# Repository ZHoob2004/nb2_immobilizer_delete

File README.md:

# nb2_immobilizer_delete

This board is meant to be installed on the connector pins inside the ECU and disable the immobilizer by providing affirmative responses even when a valid chip is not present.

To use, remove the ecu from the car and open the lid. Align the board with the main connector and solder the 3 circled points, then close and reinstall.

Leaving the factory immobilizer connected, turn the key to the on position and wait for a few seconds. Then turn the key off and disconnect the factory immobilizer module under the steering column.

The car should now start with any working key, regardless of chip pairing.

The rough design and firmware were taken from a miata.net thread, credit to Alcantor

https://forum.miata.net/vb/showthread.php?p=8561544#post8561544

# Build and flash instructions

This firmware targets a **bare ATtiny85 running at 1 MHz** using the calibrated 8 MHz internal RC oscillator with the `CKDIV8` fuse programmed.

## Toolchain

Install these tools:

- `avr-gcc`
- `avr-libc`
- `binutils-avr` / `avr-objcopy`
- `avrdude`

On Debian/Ubuntu/WSL:

```bash
sudo apt update
sudo apt install gcc-avr avr-libc binutils-avr avrdude
```

## Build

From the repository root:

```bash
avr-gcc \
  -Wall -Wextra -Os -std=gnu11 \
  -ffunction-sections -fdata-sections \
  -Wl,--gc-sections \
  -DF_CPU=1000000UL \
  -mmcu=attiny85 \
  -o main.elf main.c

avr-objcopy -j .text -j .data -O ihex main.elf main.hex
avr-objcopy -j .text -j .data -O binary main.elf main.bin
avr-size -C --mcu=attiny85 main.elf
```

`main.hex` is the recommended file for AVRDUDE. `main.bin` is also produced as a raw flash image for releases or other programming tools.

## 1 MHz clock fuse

Use low fuse **`0x62`**:

- internal calibrated 8 MHz RC oscillator
- `CKDIV8` programmed, giving a 1 MHz system clock
- clock output disabled
- default long startup delay retained

Only the low fuse needs to be changed for the 1 MHz clock configuration. Do **not** program `RSTDISBL`; the RESET pin is required for ISP.

You can read the existing fuses before changing anything:

```bash
avrdude -c arduino_as_isp -P COM5 -b 19200 -p t85 \
  -U lfuse:r:-:h -U hfuse:r:-:h -U efuse:r:-:h
```

Replace `COM5` with the programmer's serial port. On Linux/WSL this may be `/dev/ttyACM0` or `/dev/ttyUSB0`.

## Arduino as ISP

Load the standard **ArduinoISP** sketch onto the Arduino programmer first. The current ArduinoISP sketch uses a target SPI clock of approximately 166.7 kHz by default, specifically chosen to be safe for a 1 MHz ATtiny target.

### AVRDUDE 8.x / current programmer name

Set the 1 MHz fuse:

```bash
avrdude -c arduino_as_isp -P COM5 -b 19200 -p t85 \
  -U lfuse:w:0x62:m
```

Flash and verify the HEX file:

```bash
avrdude -c arduino_as_isp -P COM5 -b 19200 -p t85 \
  -U flash:w:main.hex:i \
  -U flash:v:main.hex:i
```

Or write the fuse and firmware in one command:

```bash
avrdude -c arduino_as_isp -P COM5 -b 19200 -p t85 \
  -U lfuse:w:0x62:m \
  -U flash:w:main.hex:i \
  -U flash:v:main.hex:i
```

### Older AVRDUDE installations

If your AVRDUDE does not recognize `arduino_as_isp`, use the STK500v1 programmer definition used by the ArduinoISP sketch:

```bash
avrdude -c stk500v1 -P COM5 -b 19200 -p t85 \
  -U lfuse:w:0x62:m \
  -U flash:w:main.hex:i \
  -U flash:v:main.hex:i
```

The `-b 19200` option is the serial link speed between the PC and the Arduino running ArduinoISP; it is **not** the ISP SCK frequency sent to the ATtiny.

## ISP wiring

ATtiny85 ISP signals are:

| ATtiny85 | ISP function |
|---|---|
| PB0 / pin 5 | MOSI |
| PB1 / pin 6 | MISO |
| PB2 / pin 7 | SCK |
| PB5 / pin 1 | RESET |
| pin 8 | VCC |
| pin 4 | GND |

The application signals are deliberately moved away from the ISP pins:

- `TX_INV` = PB3 / pin 2
- `RX_INV` = PB4 / pin 3

`RX_INV` has an external 10 kOhm pull-up, so the firmware does not enable the ATtiny internal pull-up on PB4.

## EEPROM note

The firmware stores the learned five-byte immobilizer response in EEPROM. A normal AVRDUDE flash operation may perform a chip erase, and the factory-default high fuse does **not** preserve EEPROM through chip erase.

If you intend to reflash a unit after it has learned a code, back up EEPROM first:

```bash
avrdude -c arduino_as_isp -P COM5 -b 19200 -p t85 \
  -U eeprom:r:eeprom-backup.hex:i
```

Restore it afterward if necessary:

```bash
avrdude -c arduino_as_isp -P COM5 -b 19200 -p t85 \
  -U eeprom:w:eeprom-backup.hex:i
```

Alternatively, the `EESAVE` high-fuse bit can be programmed so EEPROM survives chip erase, but that changes the high fuse and should be done deliberately rather than as part of the basic 1 MHz flashing command.

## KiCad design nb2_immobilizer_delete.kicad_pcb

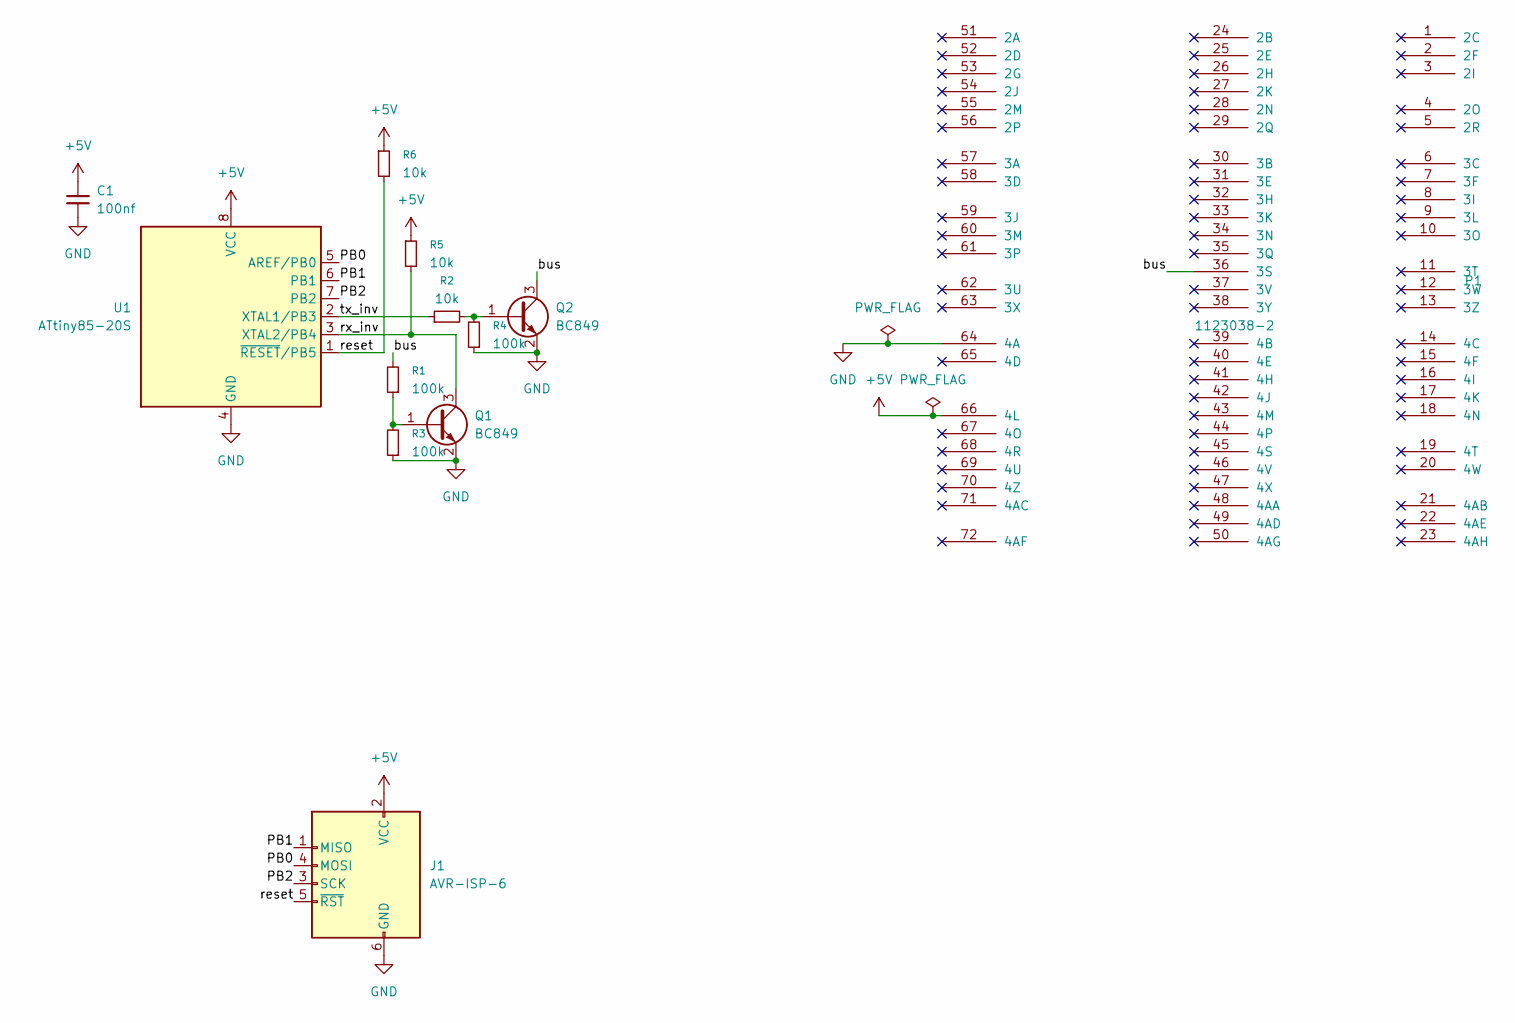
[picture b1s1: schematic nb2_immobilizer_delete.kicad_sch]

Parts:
C1: 100nf; C_0603_1608Metric
J1: AVR-ISP-6; Tag-Connect_TC2030-IDC-NL_2x03_P1.27mm_Vertical
P1: 1123038-2
Q1, Q2: BC849; SOT-23; LCSC Part # C334244
R1, R3, R4: 100k; R_0603_1608Metric; LCSC Part # C25803
R2, R5, R6: 10k; R_0603_1608Metric; LCSC Part # C25804
U1: ATtiny85-20S; SOIC-8_5.3x5.3mm_P1.27mm; LCSC Part # C31540447

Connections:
+5V: C1.1, J1.2 (VCC), P1.66 (4L), R5.1, R6.1, U1.8 (VCC)
/PB0: J1.4 (MOSI), U1.5 (AREF/PB0)
/PB1: J1.1 (MISO), U1.6 (PB1)
/PB2: J1.3 (SCK), U1.7 (PB2)
/bus: P1.36 (3S), Q2.3 (C), R1.2
/reset: J1.5 (~RST), R6.2, U1.1 (~RESET/PB5)
/rx_inv: Q1.3 (C), R5.2, U1.3 (XTAL2/PB4)
/tx_inv: R2.1, U1.2 (XTAL1/PB3)
GND: C1.2, J1.6 (GND), P1.64 (4A), Q1.2 (E), Q2.2 (E), R3.1, R4.1, U1.4 (GND)
unnamed: Q1.1 (B), R1.1, R3.2
unnamed: Q2.1 (B), R2.2, R4.2

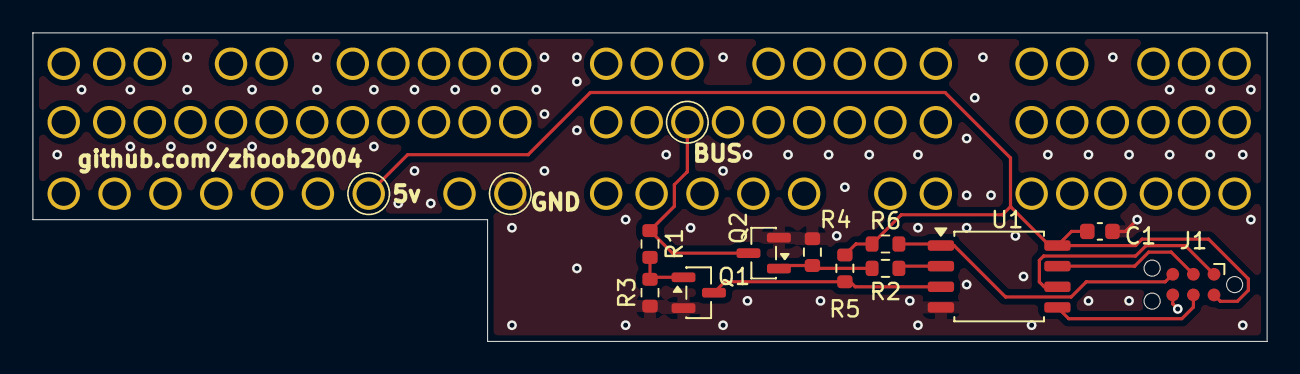
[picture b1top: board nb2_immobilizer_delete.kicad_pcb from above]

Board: 2 copper layers, 76.0 x 19.0 mm, 12 parts (1 on the bottom side), 11 nets.

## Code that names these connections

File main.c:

/**
 * MX5 NBFL Immobilizer Bypass for a bare ATtiny85.
 *
 * Target configuration:
 *   - F_CPU: 1 MHz (8 MHz internal RC oscillator with CKDIV8 enabled)
 *   - TX_INV: PB3
 *   - RX_INV: PB4, with an external 10 kOhm pull-up to VCC
 *   - PB0/PB1/PB2: reserved for ISP only
 */

#ifndef F_CPU
#define F_CPU 1000000UL
#endif

#if F_CPU != 1000000UL
#error "This firmware is configured for a 1 MHz ATtiny85 system clock."
#endif

#include <avr/io.h>
#include <avr/interrupt.h>
#include <avr/eeprom.h>
#include <stdint.h>

#define TX_INV_PIN PB3
#define RX_INV_PIN PB4

#define IMM_CODE_LEN 5

/*
 * Timer1 runs from the 1 MHz system clock divided by 8, giving a 125 kHz
 * timer clock. OCR1A/OCR1B intentionally retain the timing of the original
 * 16 MHz firmware, which used a /128 Timer1 prescaler and therefore the
 * same 125 kHz timer clock.
 */
#define TIMER1_COMPARE_A 80
#define TIMER1_COMPARE_B 105

enum state {
    s_idle,
    s_waitimm,
    s_learn,
    s_simulate
};

static volatile enum state g_state = s_idle;

#define is_reading_byte() (g_readed_bits != 0xFFFF)
#define is_writing_byte() (g_state == s_simulate)

static uint8_t g_imm_code_learn[IMM_CODE_LEN];
static volatile uint8_t g_imm_code[IMM_CODE_LEN];
static volatile uint8_t g_imm_answer_timeout;
static volatile uint8_t g_imm_learn_timeout;
static volatile uint16_t g_readed_bits = 0xFFFF;

static void handle_recv_byte(uint8_t byte);

int main(void)
{
    uint8_t data_in[2] = {1, 1};
    unsigned int i;

    cli();

    /*
     * PB3 is the only application output. Keep TX low so Q2 is off.
     * PB4 remains an input and uses the external 10 kOhm pull-up.
     * PB0/PB1/PB2 are unused during normal operation; enable their internal
     * pull-ups so the exposed ISP pads do not float when no programmer is
     * attached. During reset/ISP, the programming interface takes control.
     */
    DDRB = (1 << TX_INV_PIN);
    PORTB = (1 << PB0) | (1 << PB1) | (1 << PB2);

    /* Read the learned immobilizer code from EEPROM before enabling IRQs. */
    for (i = 0; i < IMM_CODE_LEN; ++i)
        g_imm_code[i] = eeprom_read_byte((uint8_t *)i);

    /*
     * Timer1:
     *   F_CPU = 1 MHz
     *   prescaler = 8 (CS12 = 1)
     *   timer clock = 125 kHz
     *
     * Compare A is used for receive sampling and compare B advances the
     * transmit/state-machine timing. Compare B ISR resets TCNT1 each bit.
     */
    TCCR1 = 0x00;
    TCNT1 = 0;
    OCR1A = TIMER1_COMPARE_A;
    OCR1B = TIMER1_COMPARE_B;

    /* Clear any pending Timer1 compare flags before enabling interrupts. */
    TIFR = (1 << OCF1A) | (1 << OCF1B);
    TIMSK = (1 << OCIE1A) | (1 << OCIE1B);

    /* Synchronous Timer1 clock, CK/8. */
    TCCR1 = (1 << CS12);

    sei();

    for (;;) {
        data_in[1] = data_in[0];
        data_in[0] = (PINB >> RX_INV_PIN) & 1;

        /* Synchronize Timer1 to either edge while not transmitting. */
        if (data_in[1] != data_in[0] && !is_writing_byte())
            TCNT1 = 0;
    }
}

/* Called after a complete byte is received from the bus. */
static void handle_recv_byte(uint8_t byte)
{
    static uint8_t cur_byte;
    unsigned int i;

    switch (g_state) {
    case s_idle:
        /* PCM immobilizer request. */
        if (byte == 0x0E) {
            /* Wait briefly to see whether the original immobilizer answers. */
            cur_byte = 0;
            g_imm_answer_timeout = 5;
            g_state = s_waitimm;
        }
        break;

    case s_learn:
        g_imm_code_learn[cur_byte++] = byte;
        if (cur_byte >= IMM_CODE_LEN) {
            g_state = s_idle;

            /* Store only changed bytes to reduce EEPROM wear. */
            for (i = 0; i < IMM_CODE_LEN; ++i) {
                if (g_imm_code[i] != g_imm_code_learn[i]) {
                    g_imm_code[i] = g_imm_code_learn[i];
                    eeprom_write_byte((uint8_t *)i, g_imm_code[i]);
                }
            }
        }
        break;

    default:
        break;
    }
}

/*
 * Timer1 compare A: sample at approximately 75% of the current bit period.
 * A complete frame is one start bit followed by eight data bits.
 */
ISR(TIMER1_COMPA_vect)
{
    if (is_writing_byte())
        return;

    g_readed_bits = (g_readed_bits << 1) |
                    (((uint8_t)(~PINB) >> RX_INV_PIN) & 1);

    /* Bit 9 is the inverted start bit; when it is zero, a byte is complete. */
    if ((g_readed_bits & 0x0100) == 0) {
        handle_recv_byte((uint8_t)g_readed_bits & 0xFF);
        g_readed_bits = 0xFFFF;
    }
}

/* Timer1 compare B: end-of-bit timing and transmit state machine. */
ISR(TIMER1_COMPB_vect)
{
    static uint8_t cur_byte = 0;
    static uint8_t cur_bit = 9;

    TCNT1 = 0;

    switch (g_state) {
    case s_waitimm:
        if (g_imm_answer_timeout > 0) {
            if (is_reading_byte()) {
                g_imm_learn_timeout = 176;
                g_state = s_learn;
            } else {
                --g_imm_answer_timeout;
            }
        } else {
            g_state = s_simulate;
        }
        break;

    case s_learn:
        if (g_imm_learn_timeout > 0)
            --g_imm_learn_timeout;
        else
            g_state = s_idle;
        break;

    case s_simulate:
        if (cur_bit > 9 || cur_bit == 0) {
            /* Idle/space: TX low, Q2 off, bus released. */
            PORTB &= ~(1 << TX_INV_PIN);
        } else if (cur_bit == 9) {
            /* Start bit: TX high, Q2 on, bus pulled low. */
            PORTB |= (1 << TX_INV_PIN);
        } else {
            /* Data bits, LSB first, with the external transistor inversion. */
            if (g_imm_code[cur_byte] & (1 << (cur_bit - 1)))
                PORTB &= ~(1 << TX_INV_PIN); /* Logic 1 */
            else
                PORTB |= (1 << TX_INV_PIN);  /* Logic 0 */
        }

        if (cur_bit > 0) {
            --cur_bit;
        } else {
            cur_bit = 18; /* 18..10 space, 9 start, 8..1 data, 0 idle */
            ++cur_byte;

            if (cur_byte >= IMM_CODE_LEN) {
                /* No space before the first byte; waitimm supplied the delay. */
                cur_bit = 9;
                cur_byte = 0;
                g_state = s_idle;
            }
        }
        break;

    default:
        break;
    }
}
